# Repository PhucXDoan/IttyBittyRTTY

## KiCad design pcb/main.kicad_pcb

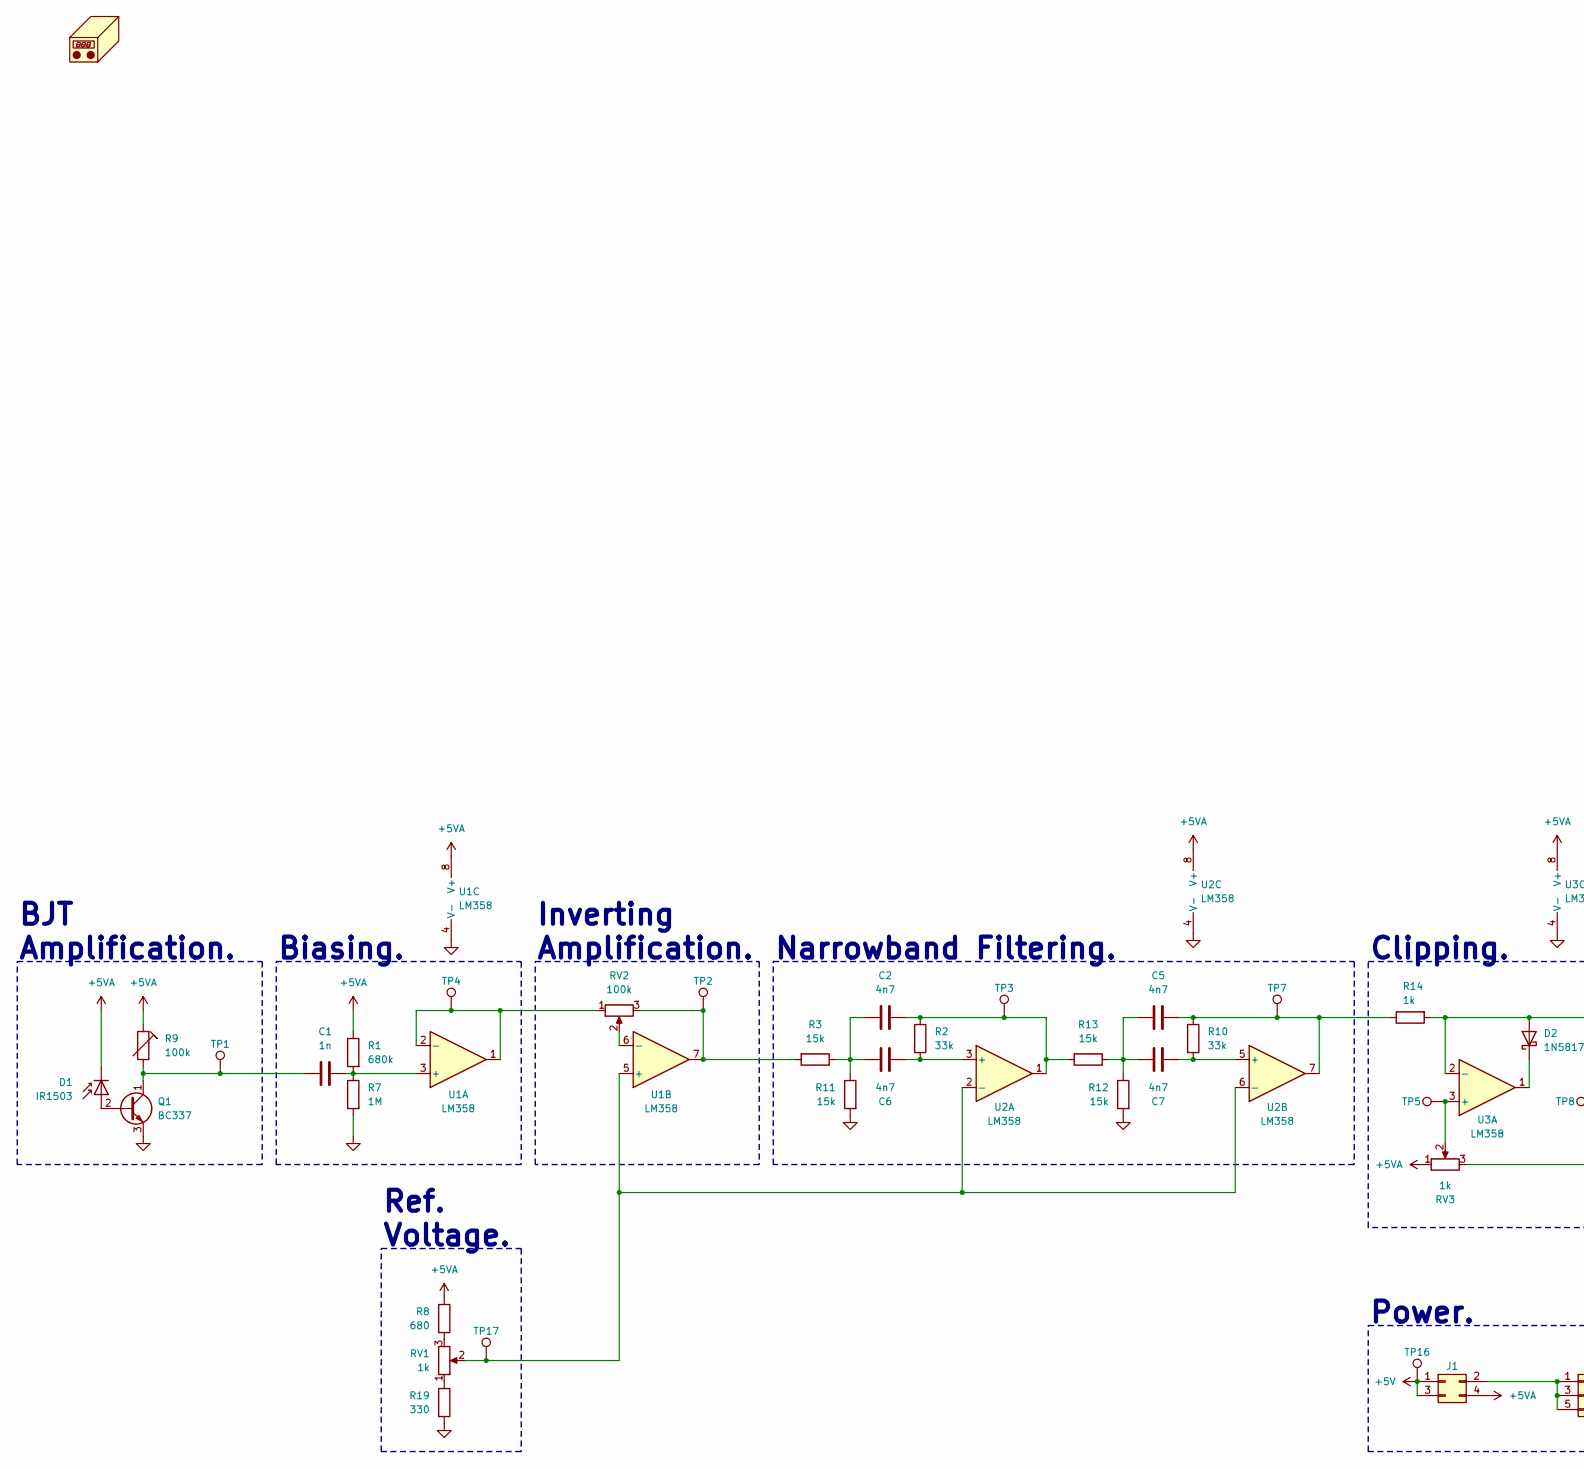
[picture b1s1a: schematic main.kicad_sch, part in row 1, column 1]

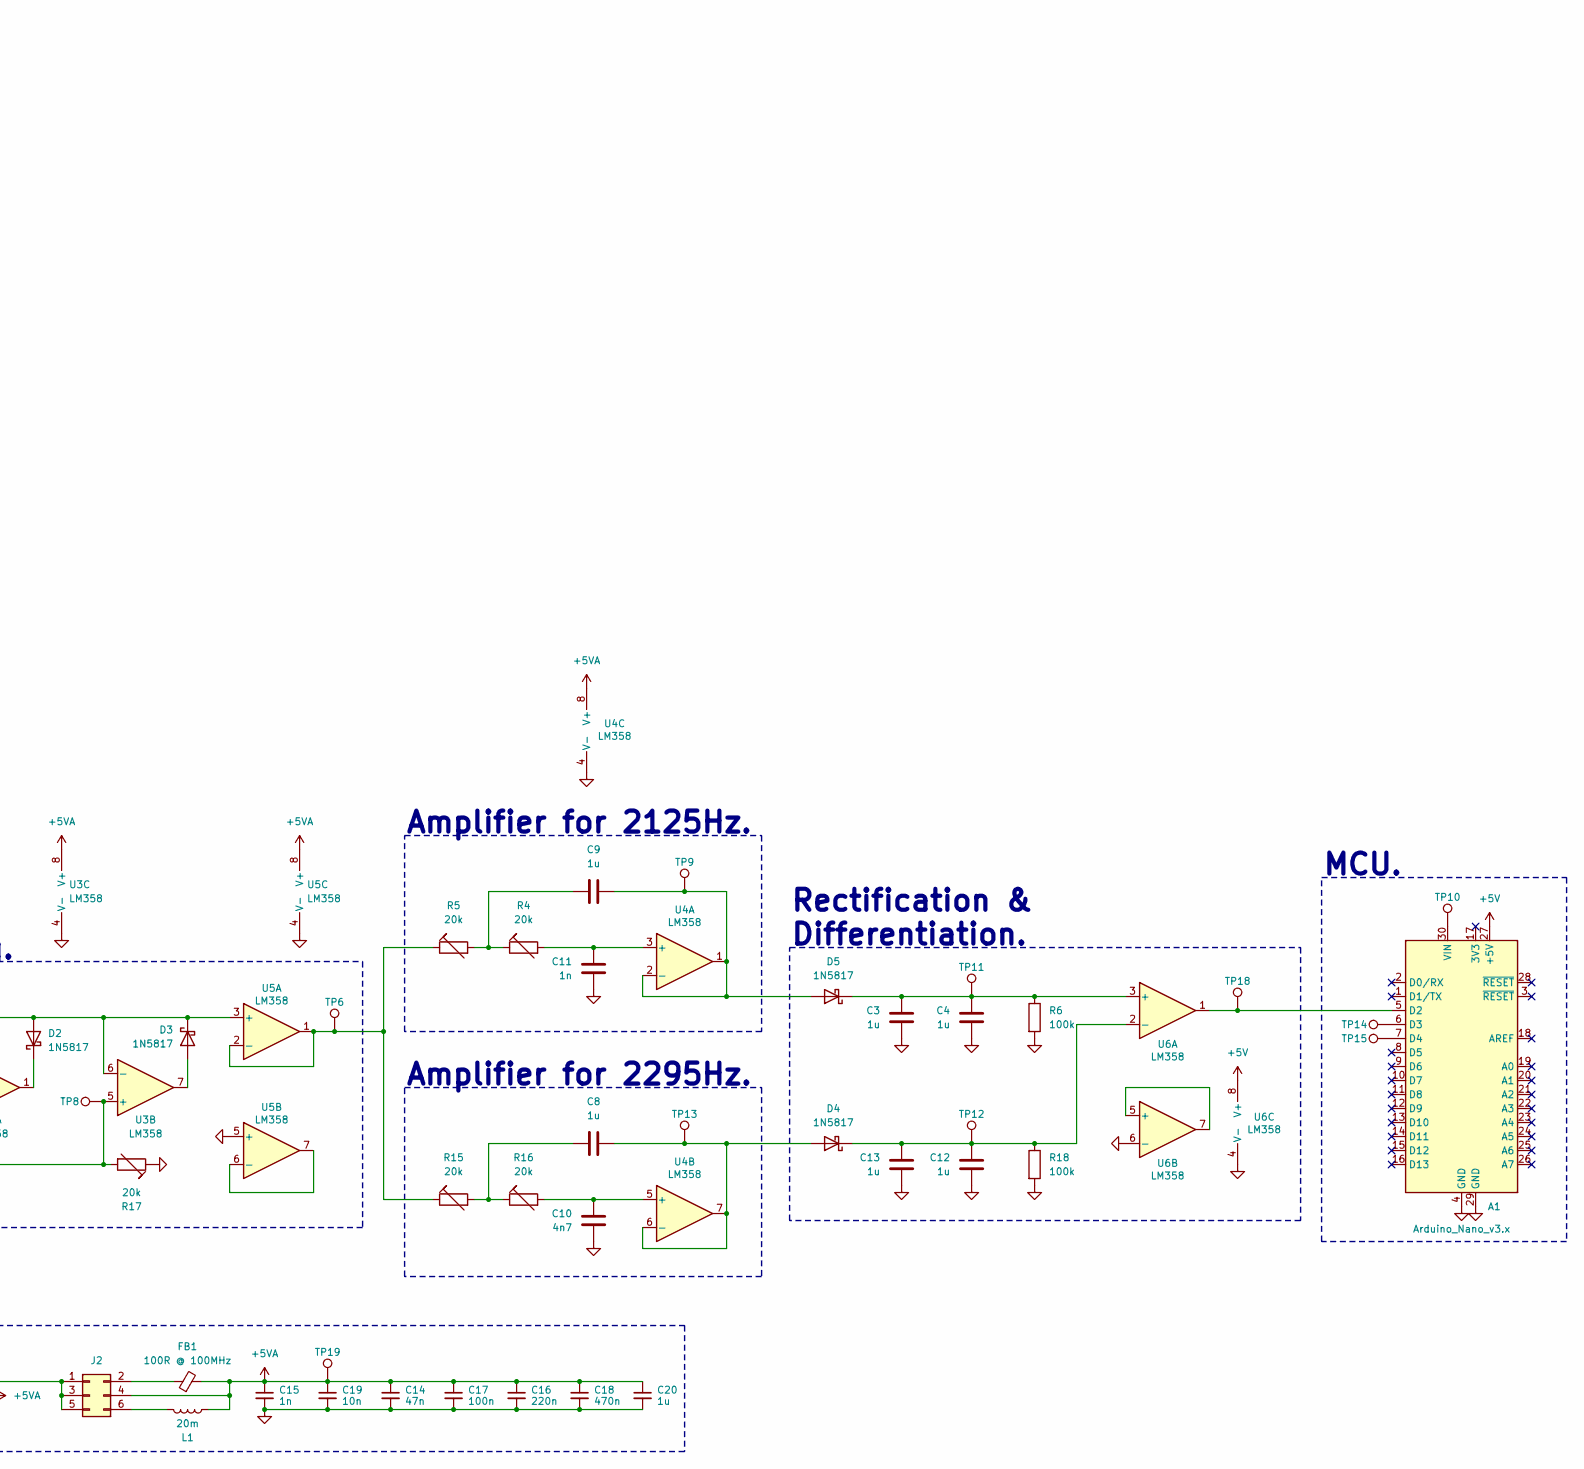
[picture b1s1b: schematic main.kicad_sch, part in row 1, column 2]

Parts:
A1: Arduino_Nano_v3.x; Arduino_Nano
C1, C11, C15: 1n; C_1206_3216Metric_Pad1.33x1.80mm_HandSolder
C2, C5, C6, C7, C10: 4n7; C_1206_3216Metric_Pad1.33x1.80mm_HandSolder
C3, C4, C8, C9, C12, C13, C20: 1u; C_1206_3216Metric_Pad1.33x1.80mm_HandSolder
C14: 47n; C_1206_3216Metric_Pad1.33x1.80mm_HandSolder
C16: 220n; C_1206_3216Metric_Pad1.33x1.80mm_HandSolder
C17: 100n; C_1206_3216Metric_Pad1.33x1.80mm_HandSolder
C18: 470n; C_1206_3216Metric_Pad1.33x1.80mm_HandSolder
C19: 10n; C_1206_3216Metric_Pad1.33x1.80mm_HandSolder
D1: IR1503; LTR-516AD
D2, D3, D4, D5: 1N5817; D_A-405_P10.16mm_Horizontal
FB1: 100R @ 100MHz; L_1206_3216Metric_Pad1.42x1.75mm_HandSolder
J1: Conn_02x02_Row_Letter_First; PinHeader_2x02_P2.54mm_Vertical
J2: Conn_02x03_Row_Letter_First; PinHeader_2x03_P2.54mm_Vertical
L1: 20m; L_Radial_D10.0mm_P5.00mm_Neosid_SD12k_style3
N1: Housing; Housing - main
Q1: BC337; TO-92_Inline
R1: 680k; R_1206_3216Metric_Pad1.30x1.75mm_HandSolder
R2, R10: 33k; R_1206_3216Metric_Pad1.30x1.75mm_HandSolder
R3, R11, R12, R13: 15k; R_1206_3216Metric_Pad1.30x1.75mm_HandSolder
R4, R5, R15, R16, R17: 20k; Trimmer 3362P
R6, R18: 100k; R_1206_3216Metric_Pad1.30x1.75mm_HandSolder
R7: 1M; R_1206_3216Metric_Pad1.30x1.75mm_HandSolder
R8: 680; R_1206_3216Metric_Pad1.30x1.75mm_HandSolder
R9: 100k; Trimmer 3362P
R14: 1k; R_1206_3216Metric_Pad1.30x1.75mm_HandSolder
R19: 330; R_1206_3216Metric_Pad1.30x1.75mm_HandSolder
RV1, RV3: 1k; Potentiometer 3362P
RV2: 100k; Potentiometer 3362P
TP1, TP2, TP3, TP4, TP5, TP6, TP7, TP8, TP9, TP10, TP11, TP12, TP13, TP14, TP15, TP16, TP17, TP18, TP19: TestPoint; TestPoint_Bridge_Pitch2.54mm_Drill0.7mm
U1, U2, U3, U4, U5, U6: LM358; SOIC-8_5.3x6.2mm_P1.27mm

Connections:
+5V: A1.27 (+5V), J1.1, J1.3, TP16.1, U6.8 (V+)
+5VA: C14.1, C15.1, C16.1, C17.1, C18.1, C19.1, C20.1, D1.1 (K), FB1.2, J1.4, J2.4, L1.1, R1.1, R8.1, R9.1, RV3.1, TP19.1, U1.8 (V+), U2.8 (V+), U3.8 (V+), U4.8 (V+), U5.8 (V+)
GND: A1.4 (GND), A1.29 (GND), C3.2, C4.2, C10.2, C11.2, C12.2, C13.2, C14.2, C15.2, C16.2, C17.2, C18.2, C19.2, C20.2, Q1.3 (E), R6.2, R7.2, R11.2, R12.2, R17.1, R18.2, R19.2, U1.4 (V-), U2.4 (V-), U3.4 (V-), U4.4 (V-), U5.4 (V-), U5.5 (+), U6.4 (V-), U6.6 (-)
unnamed: A1.5 (D2), TP18.1, U6.1
unnamed: A1.6 (D3), TP14.1
unnamed: A1.7 (D4), TP15.1
unnamed: A1.30 (VIN), TP10.1
unnamed: C2.1, C6.1, R3.1, R11.1
unnamed: C2.2, R2.1, R13.2, TP3.1, U2.1
unnamed: C5.1, C7.1, R12.1, R13.1
unnamed: C5.2, R10.1, R14.1, TP7.1, U2.7
unnamed: C8.1, R15.2, R16.1
unnamed: C9.1, R4.1, R5.2
unnamed: D1.2 (A), Q1.2 (B)
unnamed: D2.2 (A), D3.1 (K), R14.2, U3.2 (-), U3.6 (-), U5.3 (+)
unnamed: D2.1 (K), U3.1
unnamed: D3.2 (A), U3.7
unnamed: C8.2, D4.2 (A), TP13.1, U4.6 (-), U4.7
unnamed: C12.1, C13.1, D4.1 (K), R18.1, TP12.1, U6.2 (-)
unnamed: C9.2, D5.2 (A), TP9.1, U4.1, U4.2 (-)
unnamed: C3.1, C4.1, D5.1 (K), R6.1, TP11.1, U6.3 (+)
unnamed: J1.2, J2.1, J2.3, J2.5
unnamed: FB1.1, J2.2
unnamed: J2.6, L1.2
unnamed: C1.1, Q1.1 (C), R9.2, TP1.1
unnamed: R3.2, RV2.3, TP2.1, U1.7
unnamed: R8.2, RV1.3
unnamed: R19.1, RV1.1
unnamed: C1.2, R1.2, R7.1, U1.3 (+)
unnamed: RV2.1, TP4.1, U1.1, U1.2 (-)
unnamed: RV1.2, TP17.1, U1.5 (+), U2.2 (-), U2.6 (-)
unnamed: RV2.2, U1.6 (-)
unnamed: C6.2, R2.2, U2.3 (+)
unnamed: C7.2, R10.2, U2.5 (+)
unnamed: RV3.2, TP5.1, U3.3 (+)
unnamed: R17.2, RV3.3, TP8.1, U3.5 (+)
unnamed: C11.1, R4.2, U4.3 (+)
unnamed: C10.1, R16.2, U4.5 (+)
unnamed: R5.1, R15.1, TP6.1, U5.1, U5.2 (-)
unnamed: U5.6 (-), U5.7
unnamed: U6.5 (+), U6.7

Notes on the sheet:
Power.
Narrowband Filtering.
Inverting Amplification.
Amplifier for 2125Hz.
MCU.
Biasing.
Rectification & Differentiation.
Amplifier for 2295Hz.
Clipping.
Ref. Voltage.
BJT Amplification.

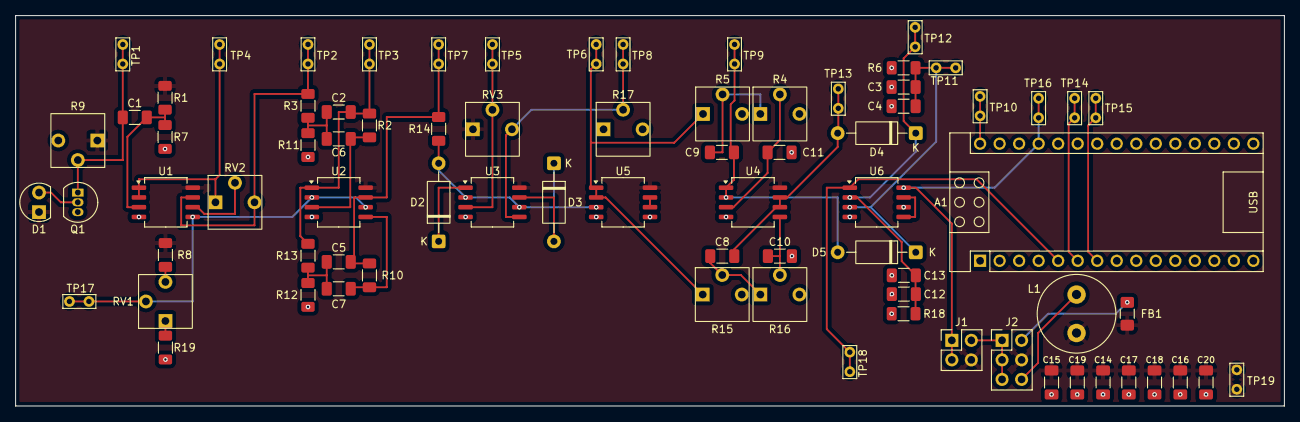
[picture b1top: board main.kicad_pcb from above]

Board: 4 copper layers, 165.1 x 50.8 mm, 79 parts (0 on the bottom side), 41 nets.

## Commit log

2025-02-01 Initial.
2025-02-03 Cleaned up script.
2025-02-03 Setting up structure.
2025-02-03 Some more meta-preprocessor stuff.
2025-02-03 Command for talking with target MCU.
2025-02-03 USART0 transmission and reception.
2025-02-03 Support for using `_delay_ms`.
2025-02-04 Table for output-compare pins.
2025-02-04 String formatting.
2025-02-04 Generating frequencies.
2025-02-06 Resetting counter value.
2025-02-19 Schematic for receiver.
2025-02-26 Using Timer1 for better accuracy.
2025-02-26 Sending string.
2025-03-04 Updated schematic.
2025-03-23 GPIO inputs.
2025-03-23 Cleaned up.
2025-03-23 Targets for transmitter and receiver.
2025-04-01 Implemented receiver filtering.
2025-04-01 Some bug fixes; more obvious receiver output.
2025-04-01 Typo.
2025-04-03 Ability to specify which COM port to use to program when there's multiple.
2025-04-19 Displaying a rolling buffer.
2025-06-13 Beginning to model an actual PCB.
2025-06-13 Added edge cuts and a model hand for size reference.
2025-06-20 Laid out first stages.
2025-06-21 Placed all components.
2025-06-23 Updated schematics with test points and power filtering.
2025-06-23 Making the Arduino Nano footprint use pin sockets.
2025-06-23 Placed the touchpoints and power stuff.
2025-07-01 Adjusted potentiometer values and reannotated.
2025-07-04 Routed things out.
